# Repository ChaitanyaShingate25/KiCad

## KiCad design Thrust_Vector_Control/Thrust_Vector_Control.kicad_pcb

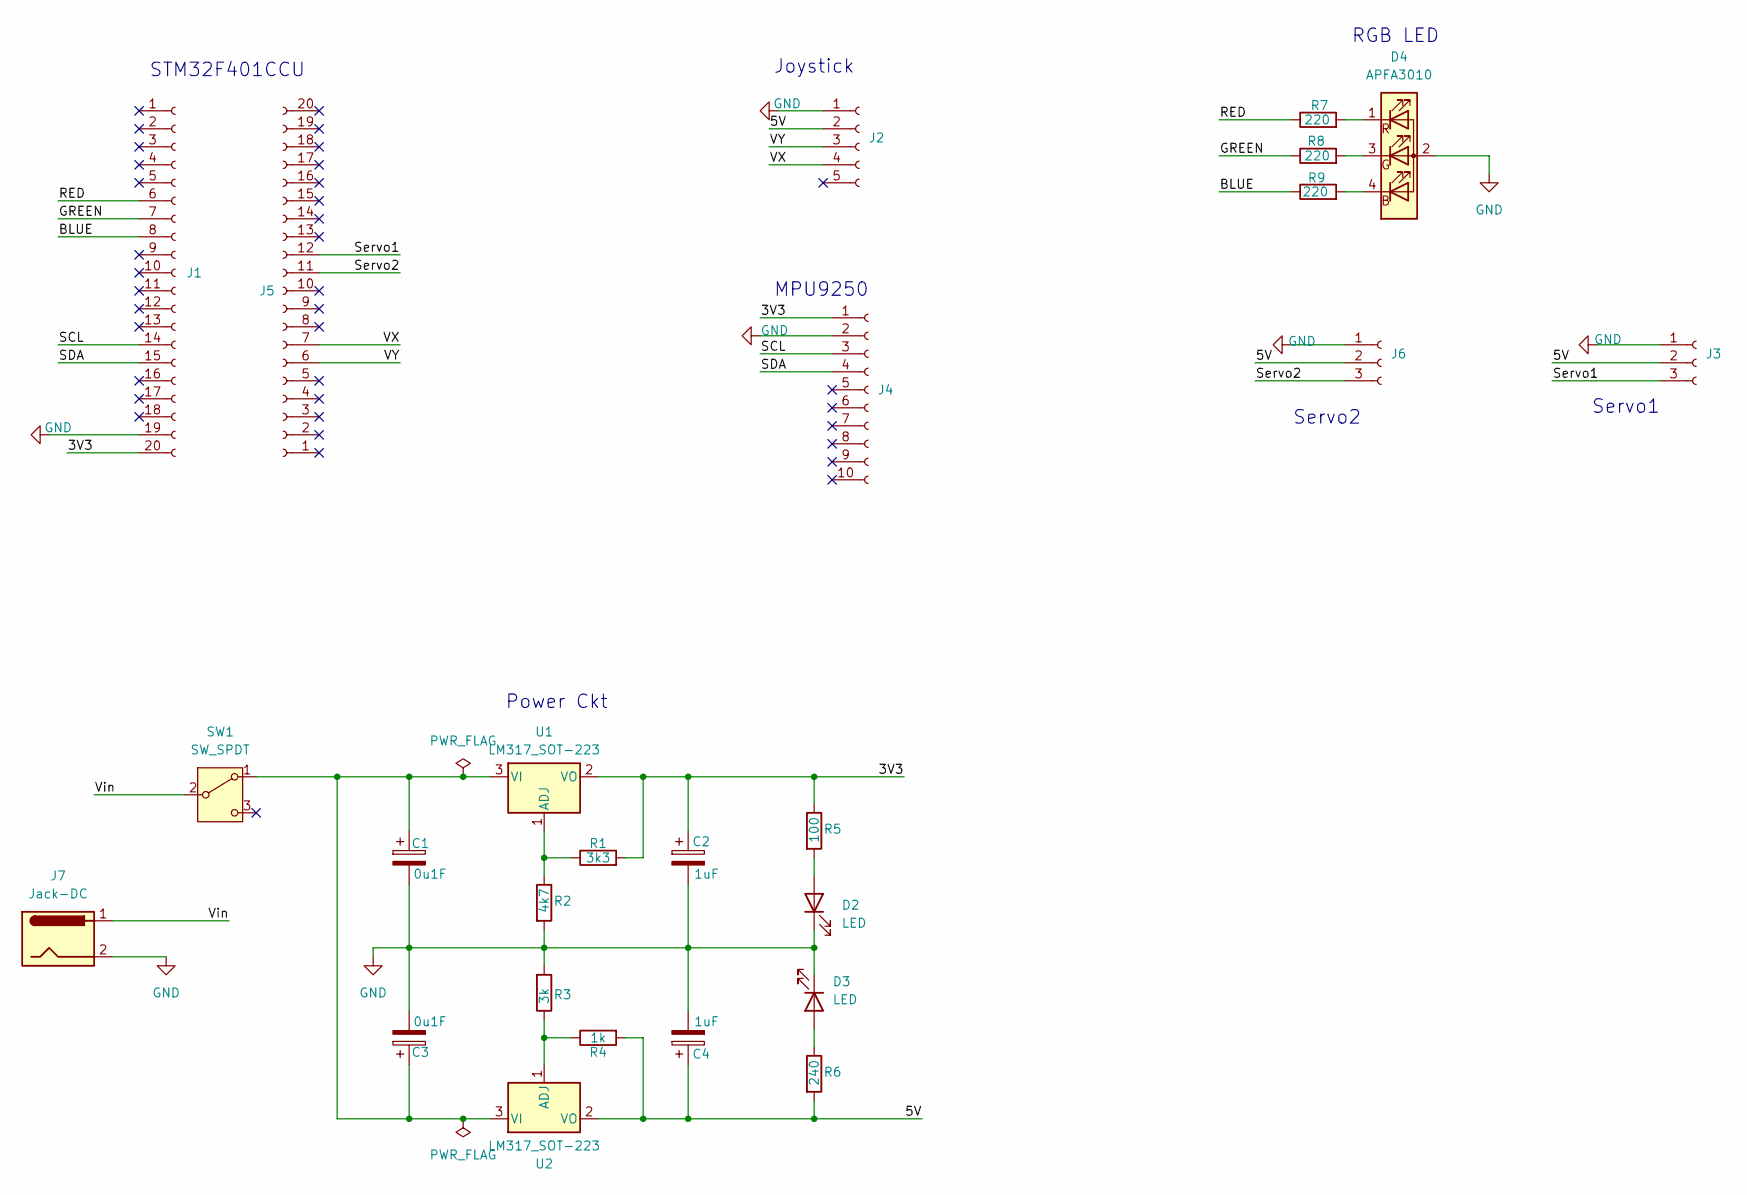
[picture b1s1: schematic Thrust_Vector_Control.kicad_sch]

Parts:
C1, C3: 0u1F; CP_Radial_D5.0mm_P2.50mm
C2, C4: 1uF; CP_Radial_D5.0mm_P2.50mm
D2, D3: LED; LED_D3.0mm
D4: APFA3010; LED_D5.0mm-4_RGB
J1: PinHeader_1x20_P2.54mm_Vertical
J2: Joystick; PinHeader_1x05_P2.54mm_Vertical
J3: Servo 1; PinHeader_1x03_P2.54mm_Vertical
J4: MPU9250; PinHeader_1x10_P2.54mm_Vertical
J5: STM32F401CCU; PinHeader_1x20_P2.54mm_Vertical
J6: Servo 2.; PinHeader_1x03_P2.54mm_Vertical
J7: Jack-DC; TerminalBlock_TE_282834-2_1x02_P2.54mm_Horizontal
R1: 3k3; R_Axial_DIN0204_L3.6mm_D1.6mm_P7.62mm_Horizontal
R2: 4k7; R_Axial_DIN0204_L3.6mm_D1.6mm_P7.62mm_Horizontal
R3: 3k; R_Axial_DIN0204_L3.6mm_D1.6mm_P7.62mm_Horizontal
R4: 1k; R_Axial_DIN0204_L3.6mm_D1.6mm_P7.62mm_Horizontal
R5: 100; R_Axial_DIN0204_L3.6mm_D1.6mm_P7.62mm_Horizontal
R6: 240; R_Axial_DIN0204_L3.6mm_D1.6mm_P7.62mm_Horizontal
R7, R8, R9: 220; R_Axial_DIN0204_L3.6mm_D1.6mm_P7.62mm_Horizontal
SW1: SW_SPDT; SW_Slide_SPDT_Straight_CK_OS102011MS2Q
U1, U2: LM317_SOT-223; TO-220-3_Vertical

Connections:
/3V3: C2.1, J1.20, J4.1, R1.2, R5.1, U1.2 (VO)
/5V: C4.1, J2.2, J3.2, J6.2, R4.2, R6.2, U2.2 (VO)
/BLUE: J1.8, R9.1
/GREEN: J1.7, R8.1
/RED: J1.6, R7.1
/SCL: J1.14, J4.3
/SDA: J1.15, J4.4
/Servo1: J3.3, J5.12
/Servo2: J5.11, J6.3
/VX: J2.4, J5.7
/VY: J2.3, J5.6
/Vin: J7.1, SW1.2 (B)
GND: C1.2, C2.2, C3.2, C4.2, D2.1 (K), D3.1 (K), D4.2 (A), J1.19, J2.1, J3.1, J4.2, J6.1, J7.2, R2.2, R3.2
unnamed: D2.2 (A), R5.2
unnamed: D3.2 (A), R6.1
unnamed: D4.4 (B), R9.2
unnamed: D4.3 (G), R8.2
unnamed: D4.1 (R), R7.2
unnamed: C1.1, C3.1, SW1.1 (A), U1.3 (VI), U2.3 (VI)
unnamed: R1.1, R2.1, U1.1 (ADJ)
unnamed: R3.1, R4.1, U2.1 (ADJ)

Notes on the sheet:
MPU9250
RGB LED
STM32F401CCU
Servo1
Joystick
Power Ckt
Servo2

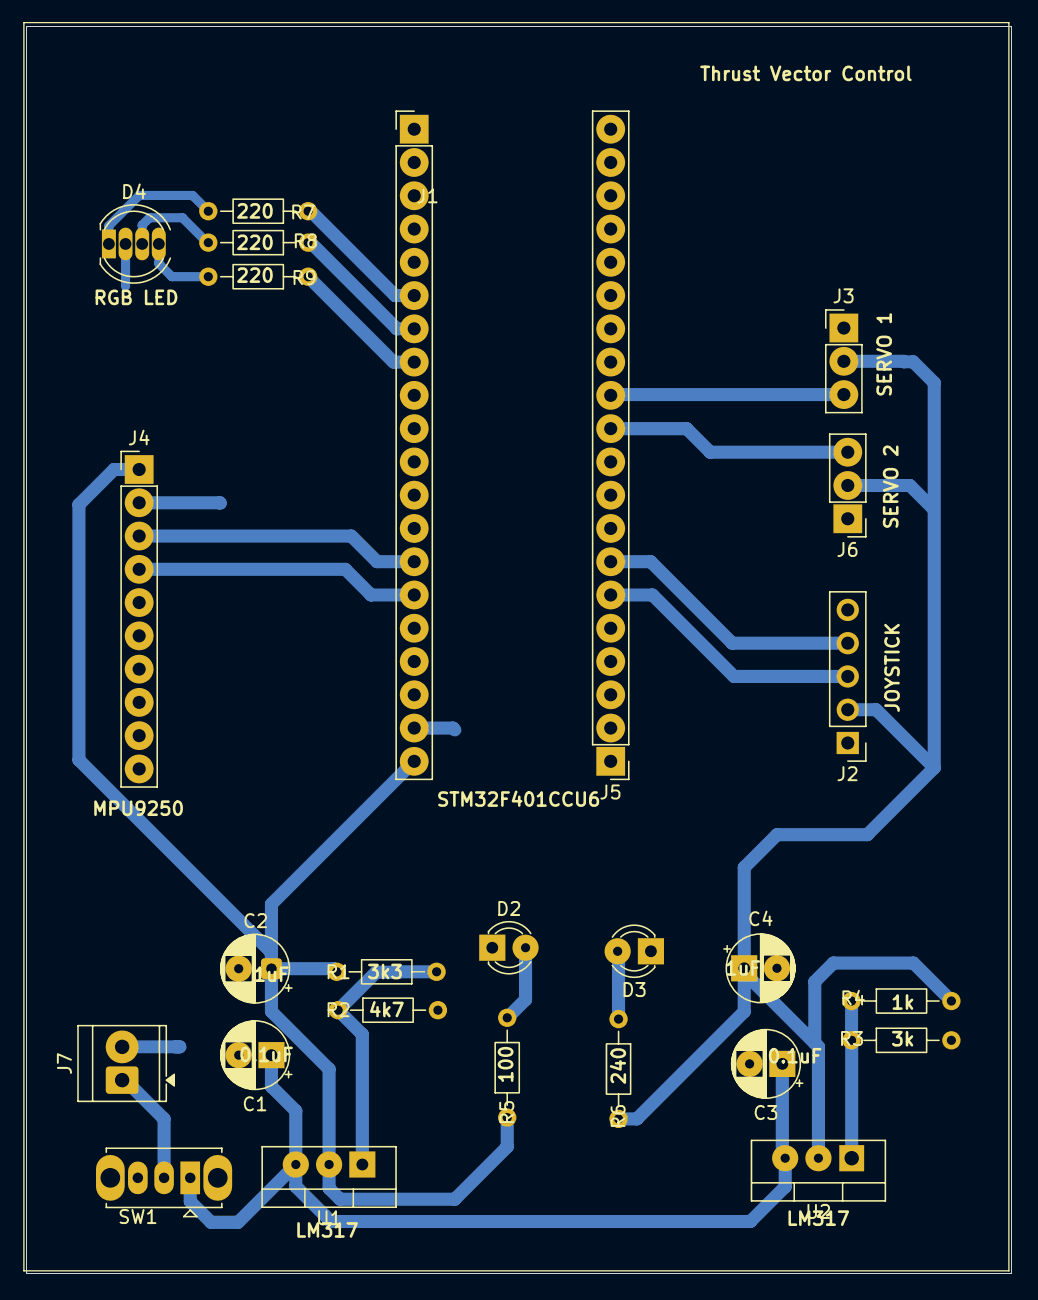
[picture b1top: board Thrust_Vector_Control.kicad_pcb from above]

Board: 2 copper layers, 75.2 x 95.2 mm, 26 parts (0 on the bottom side), 21 nets.

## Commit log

2026-04-03 PCB design for Thrust Vector Control
